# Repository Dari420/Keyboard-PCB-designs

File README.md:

# Keyboard-PCB-designs
Repository for random keyboard PCB's I design. Folders with a "!" are project folders. Folders that end with ".pretty" are libary folders. 
Gerber Files are the files you send to various PCB manufacturers in case you want to make the PCB's.
More complete and extensive projects will be in their own repositories, these are mostly prototypes and random tests.
Pretty much it, I'm a rookie so be warned that these may not be the best designs, but I hope you find at least one thing useful here :)

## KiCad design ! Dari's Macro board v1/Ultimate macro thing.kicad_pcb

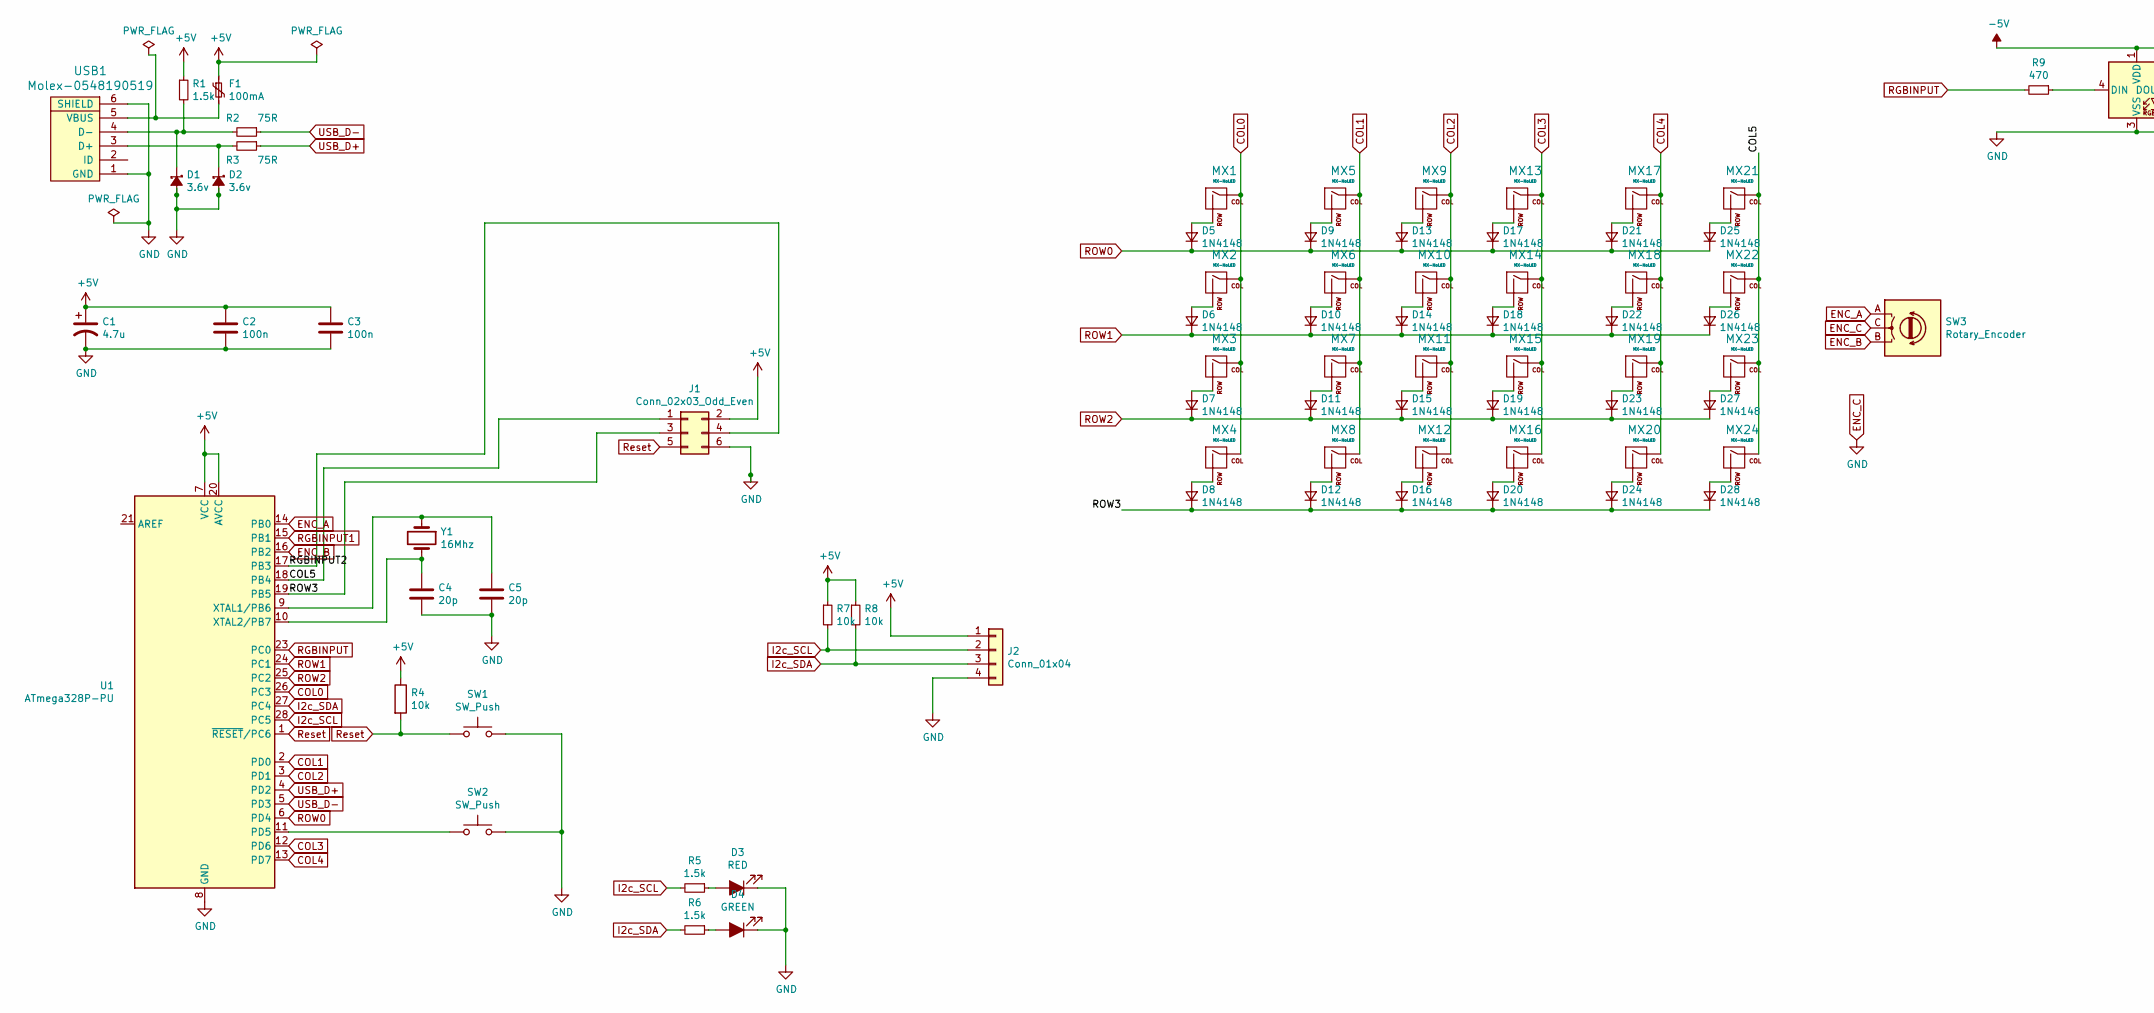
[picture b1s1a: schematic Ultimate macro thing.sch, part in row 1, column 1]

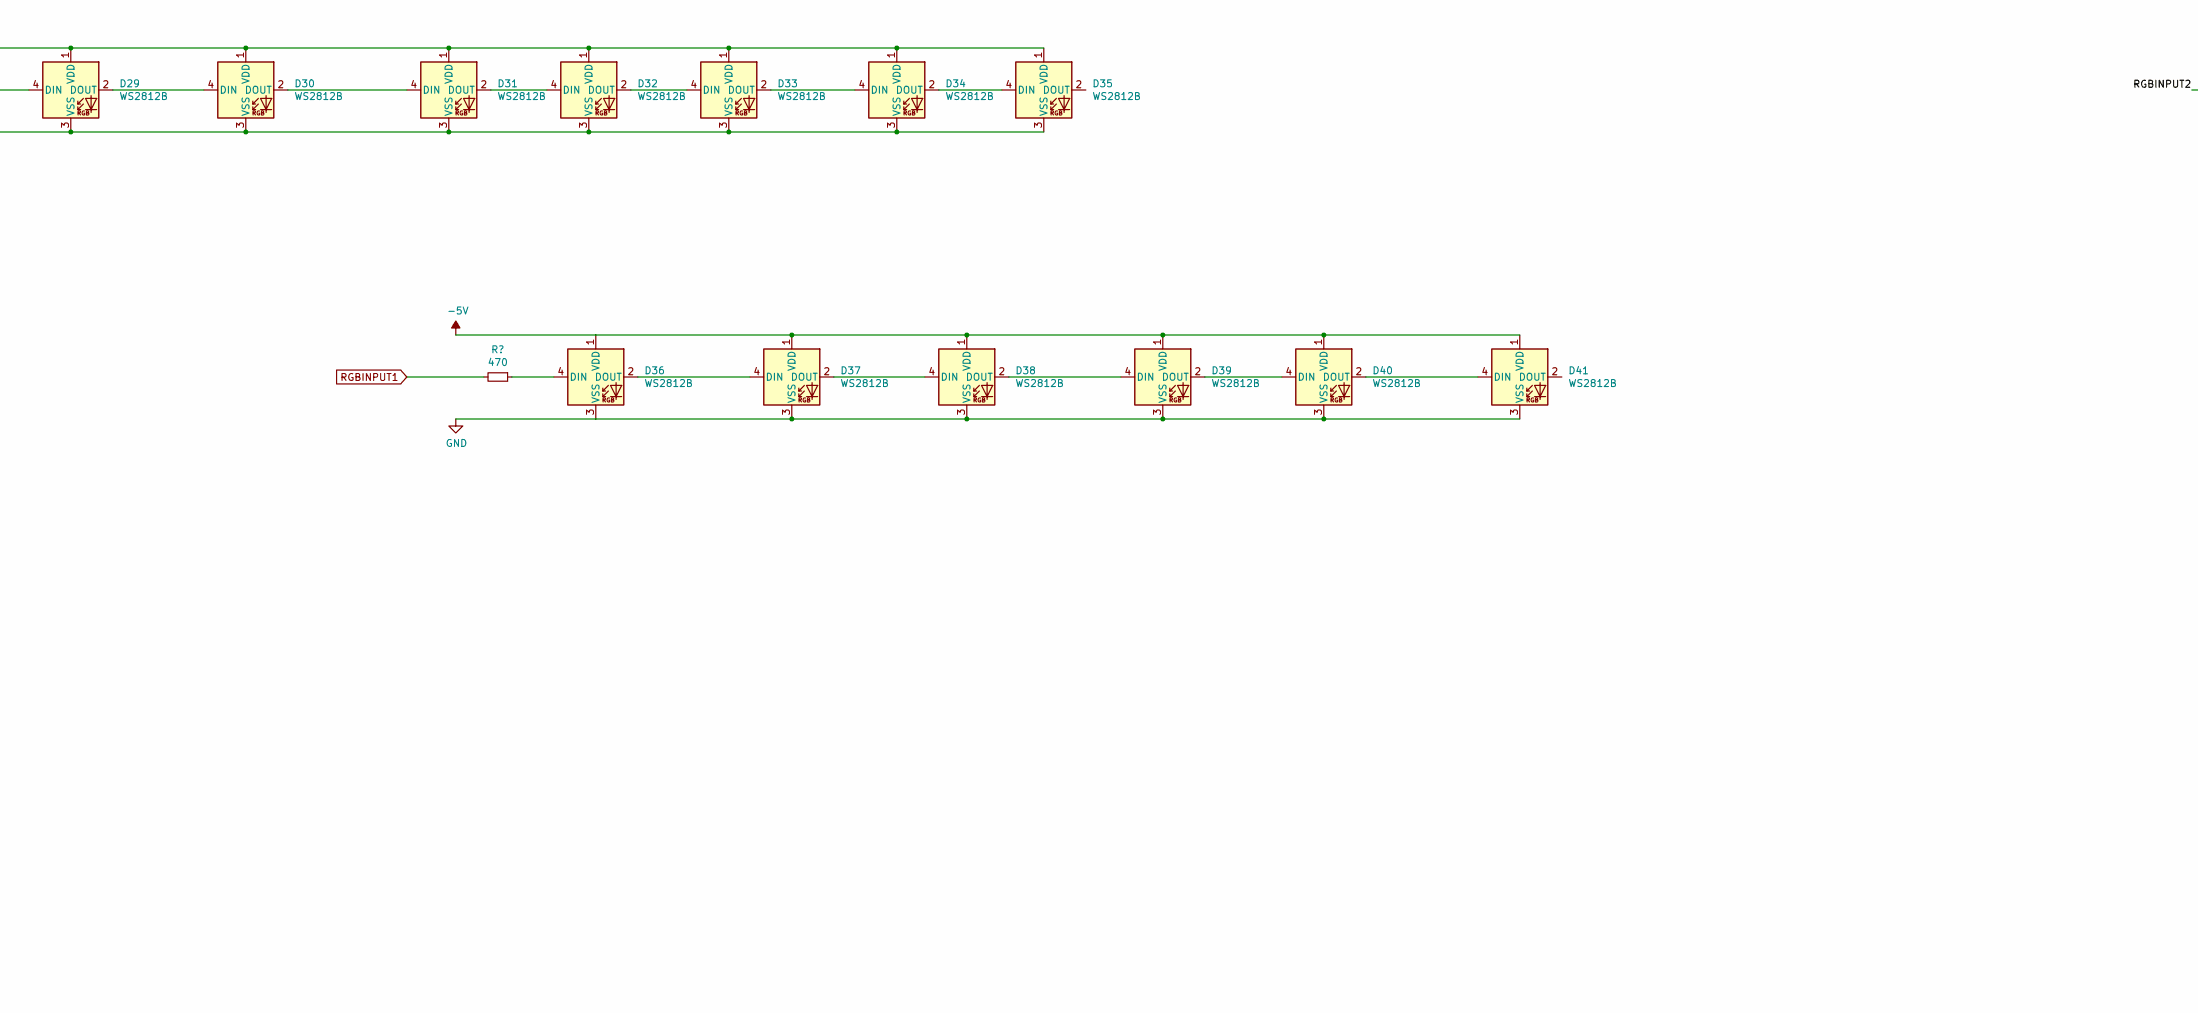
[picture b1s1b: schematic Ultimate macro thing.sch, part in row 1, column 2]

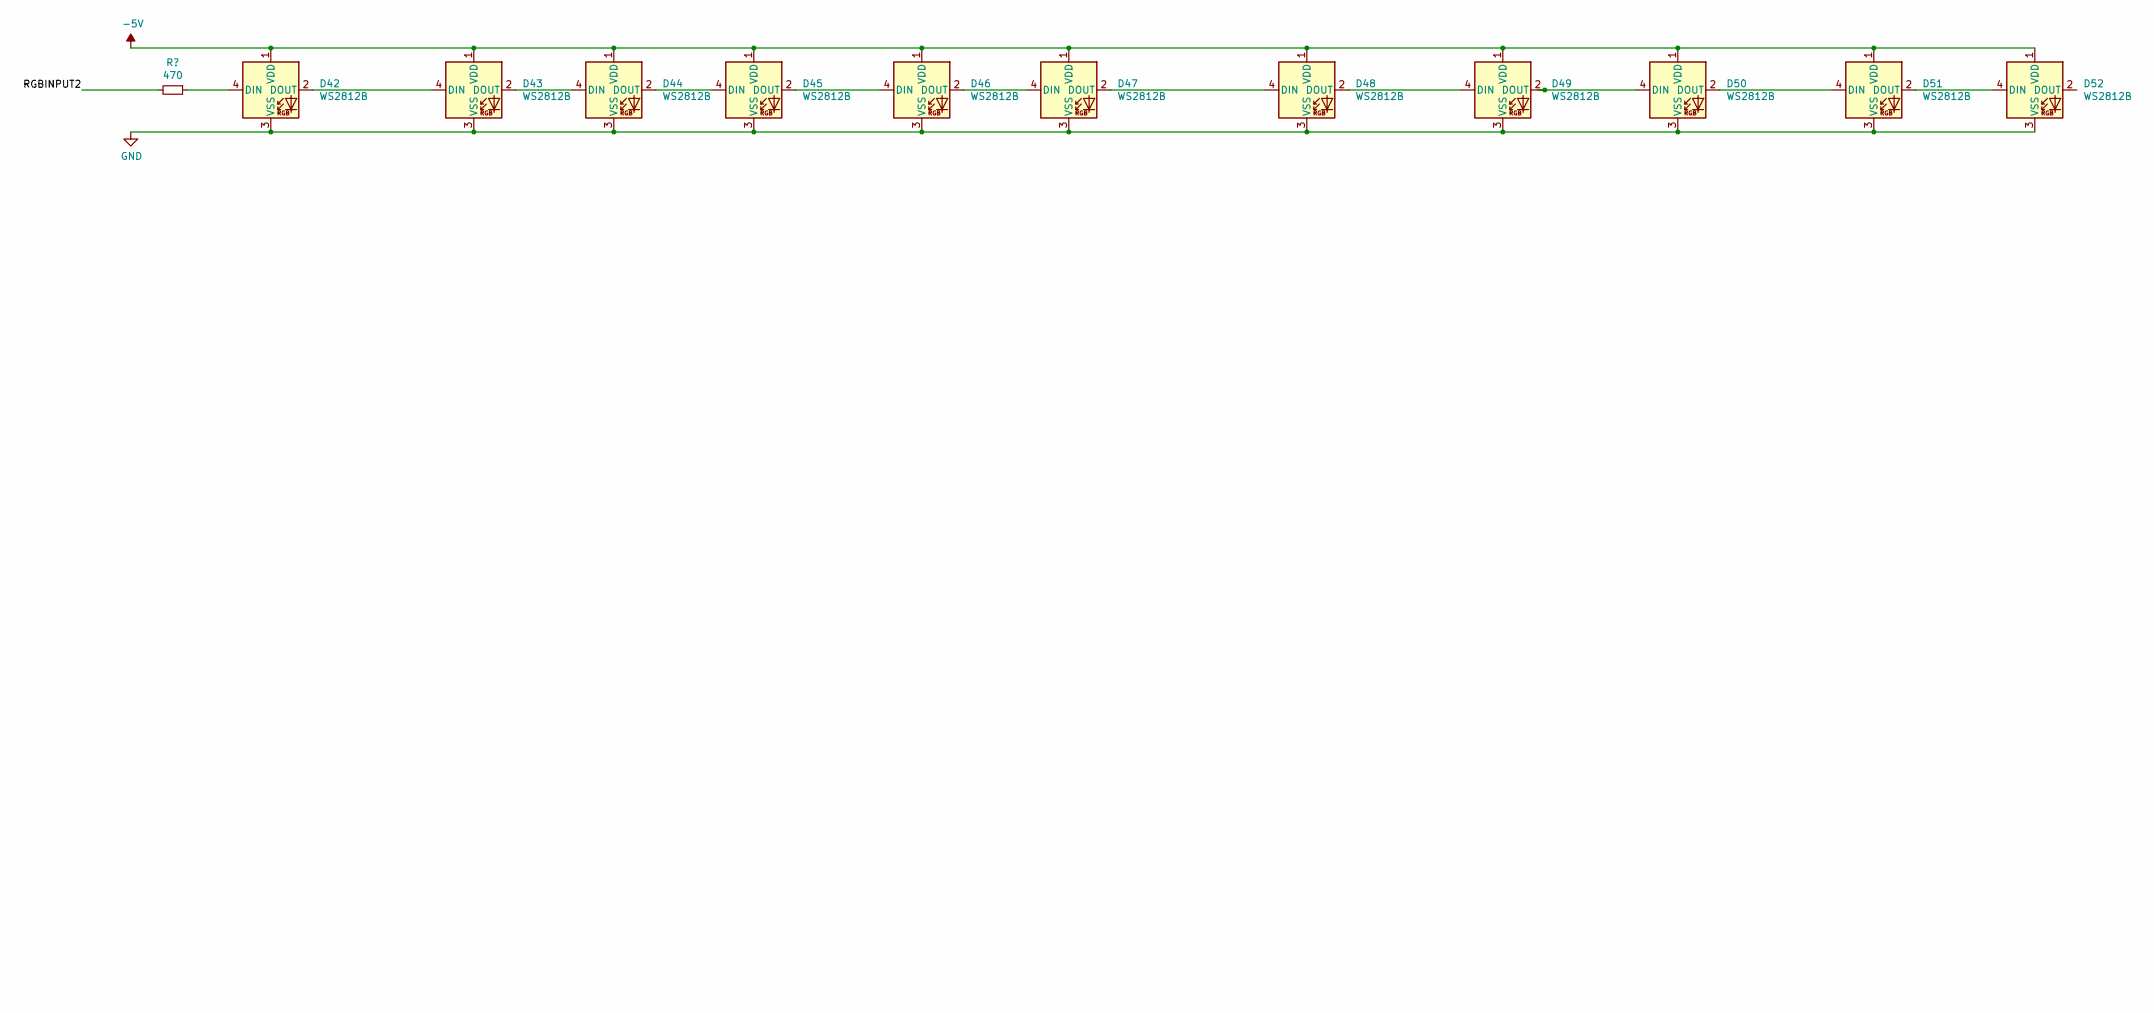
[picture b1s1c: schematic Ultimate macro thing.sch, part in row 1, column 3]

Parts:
C1: 4.7u; CP_Radial_D4.0mm_P1.50mm
C2, C3: 100n; C_Disc_D4.3mm_W1.9mm_P5.00mm
C4, C5: 20p; C_Disc_D3.0mm_W1.6mm_P2.50mm
D1, D2: 3.6v; D_DO-35_SOD27_P7.62mm_Horizontal
D3: RED; LED_D3.0mm_Clear
D4: GREEN; LED_D3.0mm_Clear
D5, D6, D7, D8, D9, D10, D11, D12, D13, D14, D15, D16, D17, D18, D19, D20, D21, D22, D23, D24, D25, D26, D27, D28: 1N4148; D_DO-35_SOD27_P7.62mm_Horizontal
D29, D30, D31, D32, D33, D34, D35, D36, D37, D38, D39, D40, D41, D42, D43, D44, D45, D46, D47, D48, D49, D50, D51, D52: WS2812B; LED_WS2812B_PLCC4_5.0x5.0mm_P3.2mm
F1: 100mA; C_Disc_D5.0mm_W2.5mm_P5.00mm
J1: Conn_02x03_Odd_Even; PinHeader_2x03_P2.54mm_Vertical
J2: Conn_01x04; PinHeader_1x04_P2.54mm_Vertical
MX1, MX2, MX3, MX4, MX5, MX6, MX7, MX8, MX9, MX10, MX11, MX12, MX13, MX14, MX15, MX16, MX17, MX18, MX19, MX20, MX21, MX22, MX23, MX24: MX-NoLED; MXOnly-1U-NoLED
R1, R5, R6: 1.5k; R_Axial_DIN0204_L3.6mm_D1.6mm_P5.08mm_Horizontal
R2, R3: 75R; R_Axial_DIN0204_L3.6mm_D1.6mm_P5.08mm_Horizontal
R4, R7, R8: 10k; R_Axial_DIN0204_L3.6mm_D1.6mm_P5.08mm_Horizontal
R9: 470; R_Axial_DIN0204_L3.6mm_D1.6mm_P5.08mm_Horizontal
SW1, SW2: SW_Push; SW_PUSH_6mm
SW3: Rotary_Encoder; RotaryEncoder_Alps_EC11E_Vertical_H20mm
U1: ATmega328P-PU; DIP-28_W7.62mm
USB1: Molex-0548190519
Y1: 16Mhz; Crystal_HC49-4H_Vertical

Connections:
+5V: C1.1, C2.1, C3.1, F1.1, J1.2, J2.1, R1.1, R4.1, R7.1, R8.1, U1.7 (VCC), U1.20 (AVCC)
-5V: D29.1 (VDD), D30.1 (VDD), D31.1 (VDD), D32.1 (VDD), D33.1 (VDD), D34.1 (VDD), D35.1 (VDD), D36.1 (VDD), D37.1 (VDD), D38.1 (VDD), D39.1 (VDD), D40.1 (VDD), D41.1 (VDD), D42.1 (VDD), D43.1 (VDD), D44.1 (VDD), D45.1 (VDD), D46.1 (VDD), D47.1 (VDD), D48.1 (VDD), D49.1 (VDD), D50.1 (VDD), D51.1 (VDD), D52.1 (VDD)
/COL5: J1.1, MX21.1 (COL), MX22.1 (COL), MX23.1 (COL), MX24.1 (COL), U1.18 (PB4)
/ROW3: D8.1 (K), D12.1 (K), D16.1 (K), D20.1 (K), D24.1 (K), D28.1 (K), J1.3, U1.19 (PB5)
COL0: MX1.1 (COL), MX2.1 (COL), MX3.1 (COL), MX4.1 (COL), U1.26 (PC3)
COL1: MX5.1 (COL), MX6.1 (COL), MX7.1 (COL), MX8.1 (COL), U1.2 (PD0)
COL2: MX9.1 (COL), MX10.1 (COL), MX11.1 (COL), MX12.1 (COL), U1.3 (PD1)
COL3: MX13.1 (COL), MX14.1 (COL), MX15.1 (COL), MX16.1 (COL), U1.12 (PD6)
COL4: MX17.1 (COL), MX18.1 (COL), MX19.1 (COL), MX20.1 (COL), U1.13 (PD7)
ENC_A: SW3.A, U1.14 (PB0)
ENC_B: SW3.B, U1.16 (PB2)
I2c_SCL: J2.2, R5.2, R7.2, U1.28 (PC5)
I2c_SDA: J2.3, R6.2, R8.2, U1.27 (PC4)
unnamed: C4.1, U1.10 (XTAL2/PB7), Y1.2
unnamed: C5.1, U1.9 (XTAL1/PB6), Y1.1
unnamed: D1.1 (K), R1.2, R2.2, USB1.4 (D-)
unnamed: D2.1 (K), R3.2, USB1.3 (D+)
unnamed: D3.2 (A), R5.1
unnamed: D4.2 (A), R6.1
unnamed: D5.2 (A), MX1.2 (ROW)
unnamed: D6.2 (A), MX2.2 (ROW)
unnamed: D7.2 (A), MX3.2 (ROW)
unnamed: D8.2 (A), MX4.2 (ROW)
unnamed: D9.2 (A), MX5.2 (ROW)
unnamed: D10.2 (A), MX6.2 (ROW)
unnamed: D11.2 (A), MX7.2 (ROW)
unnamed: D12.2 (A), MX8.2 (ROW)
unnamed: D13.2 (A), MX9.2 (ROW)
unnamed: D14.2 (A), MX10.2 (ROW)
unnamed: D15.2 (A), MX11.2 (ROW)
unnamed: D16.2 (A), MX12.2 (ROW)
unnamed: D17.2 (A), MX13.2 (ROW)
unnamed: D18.2 (A), MX14.2 (ROW)
unnamed: D19.2 (A), MX15.2 (ROW)
unnamed: D20.2 (A), MX16.2 (ROW)
unnamed: D21.2 (A), MX17.2 (ROW)
unnamed: D22.2 (A), MX18.2 (ROW)
unnamed: D23.2 (A), MX19.2 (ROW)
unnamed: D24.2 (A), MX20.2 (ROW)
unnamed: D25.2 (A), MX21.2 (ROW)
unnamed: D26.2 (A), MX22.2 (ROW)
unnamed: D27.2 (A), MX23.2 (ROW)
unnamed: D28.2 (A), MX24.2 (ROW)
unnamed: D29.2 (DOUT), D30.4 (DIN)
unnamed: D29.4 (DIN), R9.1
unnamed: D30.2 (DOUT), D31.4 (DIN)
unnamed: D31.2 (DOUT), D32.4 (DIN)
unnamed: D32.2 (DOUT), D33.4 (DIN)
unnamed: D33.2 (DOUT), D34.4 (DIN)
unnamed: D34.2 (DOUT), D35.4 (DIN)
unnamed: D35.2 (DOUT), D36.4 (DIN)
unnamed: D36.2 (DOUT), D37.4 (DIN)
unnamed: D37.2 (DOUT), D38.4 (DIN)
unnamed: D38.2 (DOUT), D39.4 (DIN)
unnamed: D39.2 (DOUT), D40.4 (DIN)
unnamed: D40.2 (DOUT), D41.4 (DIN)
unnamed: D41.2 (DOUT), D42.4 (DIN)
unnamed: D42.2 (DOUT), D43.4 (DIN)
unnamed: D43.2 (DOUT), D44.4 (DIN)
unnamed: D44.2 (DOUT), D45.4 (DIN)
unnamed: D45.2 (DOUT), D46.4 (DIN)
unnamed: D46.2 (DOUT), D47.4 (DIN)
unnamed: D47.2 (DOUT), D48.4 (DIN)
unnamed: D48.2 (DOUT), D49.4 (DIN)
unnamed: D49.2 (DOUT), D50.4 (DIN)
unnamed: D50.2 (DOUT), D51.4 (DIN)
unnamed: D51.2 (DOUT), D52.4 (DIN)
unnamed: F1.2, USB1.5 (VBUS)
unnamed: J1.4, U1.17 (PB3)
unnamed: SW2.1, U1.11 (PD5)
RGBINPUT: R9.2, U1.23 (PC0)
ROW0: D5.1 (K), D9.1 (K), D13.1 (K), D17.1 (K), D21.1 (K), D25.1 (K), U1.6 (PD4)
ROW1: D6.1 (K), D10.1 (K), D14.1 (K), D18.1 (K), D22.1 (K), D26.1 (K), U1.24 (PC1)
ROW2: D7.1 (K), D11.1 (K), D15.1 (K), D19.1 (K), D23.1 (K), D27.1 (K), U1.25 (PC2)
Reset: J1.5, R4.2, SW1.1, U1.1 (~RESET~/PC6)
USB_D+: R3.1, U1.4 (PD2)
USB_D-: R2.1, U1.5 (PD3)

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
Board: 2 copper layers, 99 parts (0 on the bottom side), 79 nets, no tracks yet.

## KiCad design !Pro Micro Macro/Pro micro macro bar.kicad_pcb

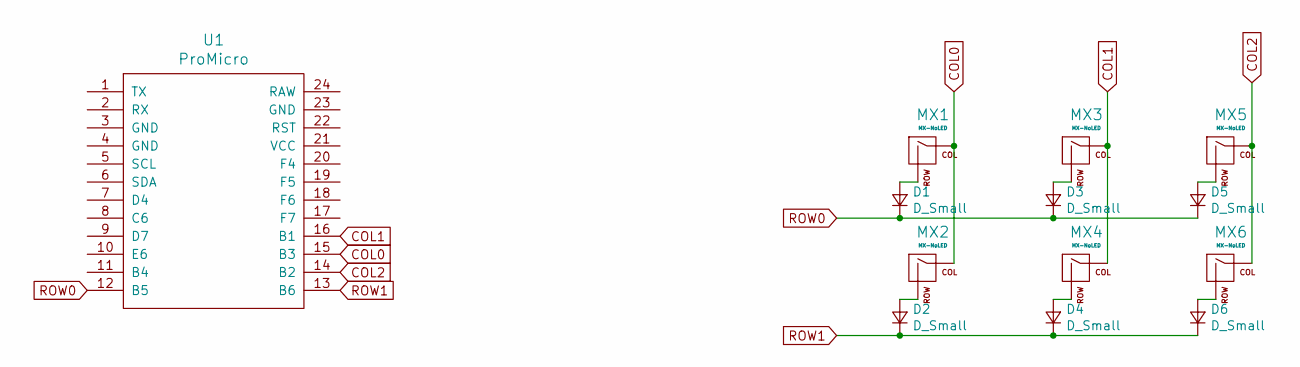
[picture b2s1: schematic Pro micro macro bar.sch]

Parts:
D1, D2, D3, D4, D5, D6: D_Small; D_SOD-123-Pretty
MX1, MX2, MX3, MX4, MX5, MX6: MX-NoLED; MXOnly-1U-Hotswap
U1: ProMicro

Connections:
COL0: MX1.1 (COL), MX2.1 (COL), U1.15 (B3)
COL1: MX3.1 (COL), MX4.1 (COL), U1.16 (B1)
COL2: MX5.1 (COL), MX6.1 (COL), U1.14 (B2)
unnamed: D1.2 (A), MX1.2 (ROW)
unnamed: D2.2 (A), MX2.2 (ROW)
unnamed: D3.2 (A), MX3.2 (ROW)
unnamed: D4.2 (A), MX4.2 (ROW)
unnamed: D5.2 (A), MX5.2 (ROW)
unnamed: D6.2 (A), MX6.2 (ROW)
ROW0: D1.1 (K), D3.1 (K), D5.1 (K), U1.12 (B5)
ROW1: D2.1 (K), D4.1 (K), D6.1 (K), U1.13 (B6)

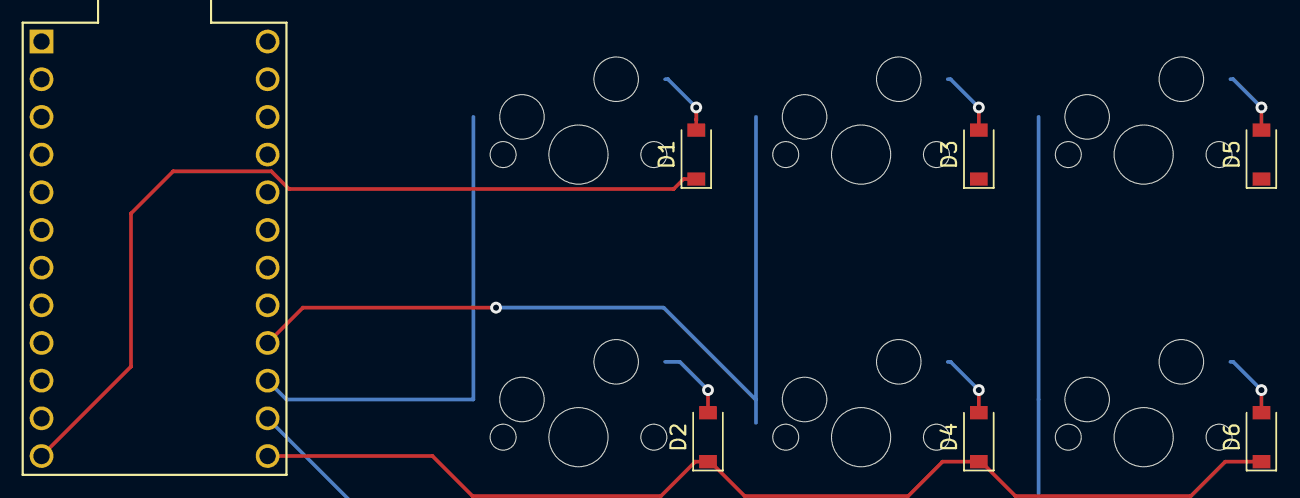
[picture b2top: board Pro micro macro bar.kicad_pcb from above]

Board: 2 copper layers, 13 parts (0 on the bottom side), 11 nets.

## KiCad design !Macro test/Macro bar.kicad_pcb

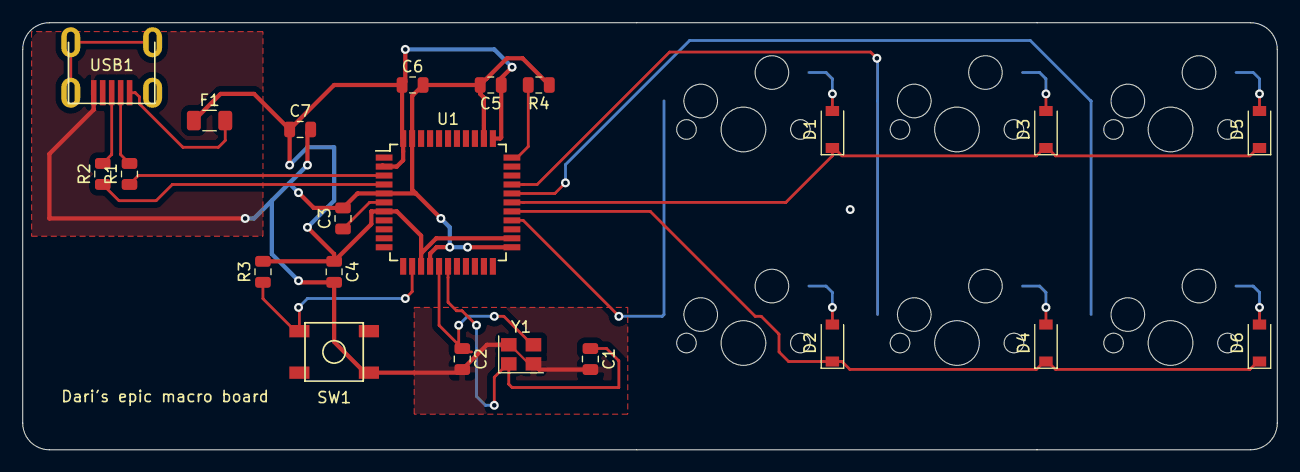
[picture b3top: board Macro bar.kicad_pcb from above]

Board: 2 copper layers, 111.9 x 38.1 mm, 28 parts (0 on the bottom side), 23 nets.

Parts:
C1, C2: 22pf; C_0805_2012Metric
C3: 1uF; C_0805_2012Metric
C4, C5, C6: 0.1uF; C_0805_2012Metric
C7: 10uF; C_0805_2012Metric
D1, D2, D3, D4, D5, D6: D_Small; D_SOD-123
F1: 500mA; Fuse_1206_3216Metric
MX1, MX2, MX3, MX4, MX5, MX6: MX-NoLED; MXOnly-1U-Hotswap
R1, R2: 22; R_0805_2012Metric
R3, R4: 10k; R_0805_2012Metric
SW1: SW_Push; SKQG-1155865
U1: ATmega32U4-AU; TQFP-44_10x10mm_P0.8mm
USB1: Molex-0548190589
Y1: 16MHz; Crystal_SMD_3225-4Pin_3.2x2.5mm

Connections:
+5V: C4.1, C5.1, C6.1, C7.1, F1.1, R3.2, U1.2, U1.7, U1.14, U1.24, U1.34, U1.44
COL0: MX1.1, MX2.1, U1.26
COL1: MX3.1, MX4.1, U1.30
COL3: MX5.1, MX6.1, U1.29
D+: R2.2, USB1.3
D-: R1.2, USB1.4
GND: C1.2, C2.2, C3.2, C4.2, C5.2, C6.2, C7.2, R4.1, SW1.1, U1.5, U1.15, U1.23, U1.35, U1.43, USB1.1, Y1.2, Y1.4
unnamed: C1.1, U1.17, Y1.1
unnamed: C2.1, U1.16, Y1.3
unnamed: C3.1, U1.6
unnamed: D1.2, MX1.2
unnamed: D2.2, MX2.2
unnamed: D3.2, MX3.2
unnamed: D4.2, MX4.2
unnamed: D5.2, MX5.2
unnamed: D6.2, MX6.2
unnamed: R1.1, U1.3
unnamed: R2.1, U1.4
unnamed: R3.1, SW1.2, U1.13
unnamed: R4.2, U1.33
ROW0: D1.1, D3.1, D5.1, U1.28
ROW1: D2.1, D4.1, D6.1, U1.27
VCC: F1.2, USB1.5

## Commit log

2019-10-23 Complete reorginization
2019-10-23 wiring in process
2019-10-23 Reoriginization
2019-10-24 Linked encoder
2019-10-26 Redesign
2019-11-15 Redesigned pro micro
2020-01-18 deleted useless projects
